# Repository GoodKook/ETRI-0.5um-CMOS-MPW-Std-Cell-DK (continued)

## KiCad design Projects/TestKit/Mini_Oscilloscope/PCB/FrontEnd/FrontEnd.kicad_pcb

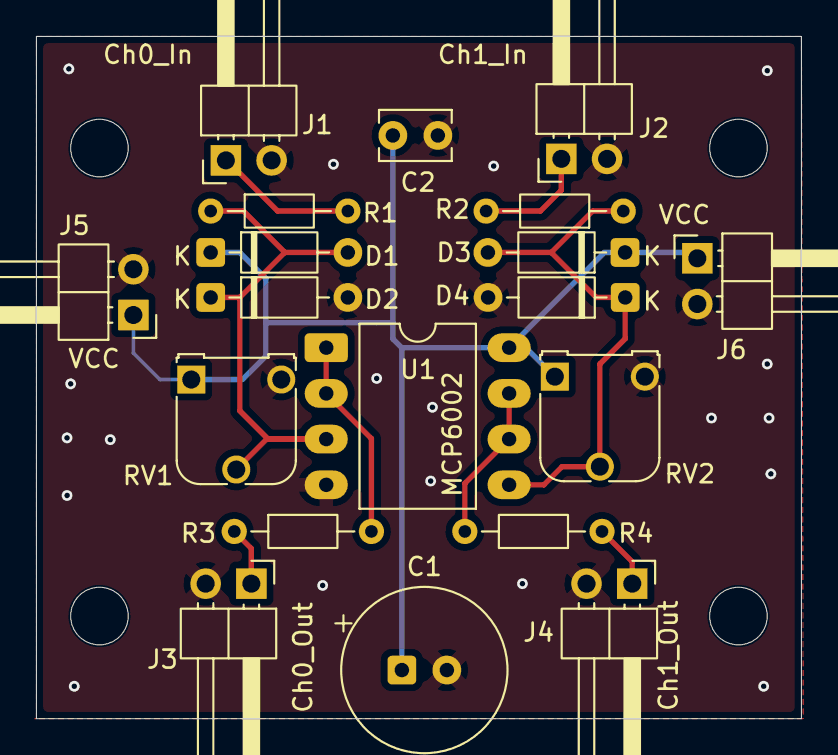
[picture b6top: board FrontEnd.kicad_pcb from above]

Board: 2 copper layers, 42.5 x 37.9 mm, 23 parts (0 on the bottom side), 10 nets.

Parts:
C1: 10u; CP_Radial_Tantal_D9.0mm_P2.50mm
C2: 100n; C_Disc_D3.8mm_W2.6mm_P2.50mm
D1, D2, D3, D4: 1N4148; D_DO-35_SOD27_P7.62mm_Horizontal
J1: Ch0_In; PinHeader_1x02_P2.54mm_Horizontal
J2: Ch1_In; PinHeader_1x02_P2.54mm_Horizontal
J3: Ch0_Out; PinHeader_1x02_P2.54mm_Horizontal
J4: Ch1_Out; PinHeader_1x02_P2.54mm_Horizontal
J5, J6: VCC; PinHeader_1x02_P2.54mm_Horizontal
R1, R2: 680K; R_Axial_DIN0204_L3.6mm_D1.6mm_P7.62mm_Horizontal
R3, R4: 100; R_Axial_DIN0204_L3.6mm_D1.6mm_P7.62mm_Horizontal
RV1, RV2: 1M; Potentiometer_Runtron_RM-065_Vertical
TP1, TP2, TP3, TP4: Mounting Hole; MountingHole_3.2mm_M3
U1: MCP6002; DIP-8_W10.16mm_LongPads

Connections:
/ADC_0: J3.1, R3.1
/ADC_1: J4.1, R4.1
GND: C1.2, C2.2, D2.2 (A), D4.2 (A), J1.2, J2.2, J3.2, J4.2, J5.2, J6.2, RV1.3, RV2.3, U1.4 (V-)
unnamed: D1.2 (A), D2.1 (K), R1.1, RV1.2, U1.3 (+)
unnamed: D3.2 (A), D4.1 (K), R2.1, RV2.2, U1.5 (+)
unnamed: J1.1, R1.2
unnamed: J2.1, R2.2
unnamed: R3.2, U1.1, U1.2 (-)
unnamed: R4.2, U1.6 (-), U1.7
VCC: C1.1, C2.1, D1.1 (K), D3.1 (K), J5.1, J6.1, RV1.1, RV2.1, U1.8 (V+)

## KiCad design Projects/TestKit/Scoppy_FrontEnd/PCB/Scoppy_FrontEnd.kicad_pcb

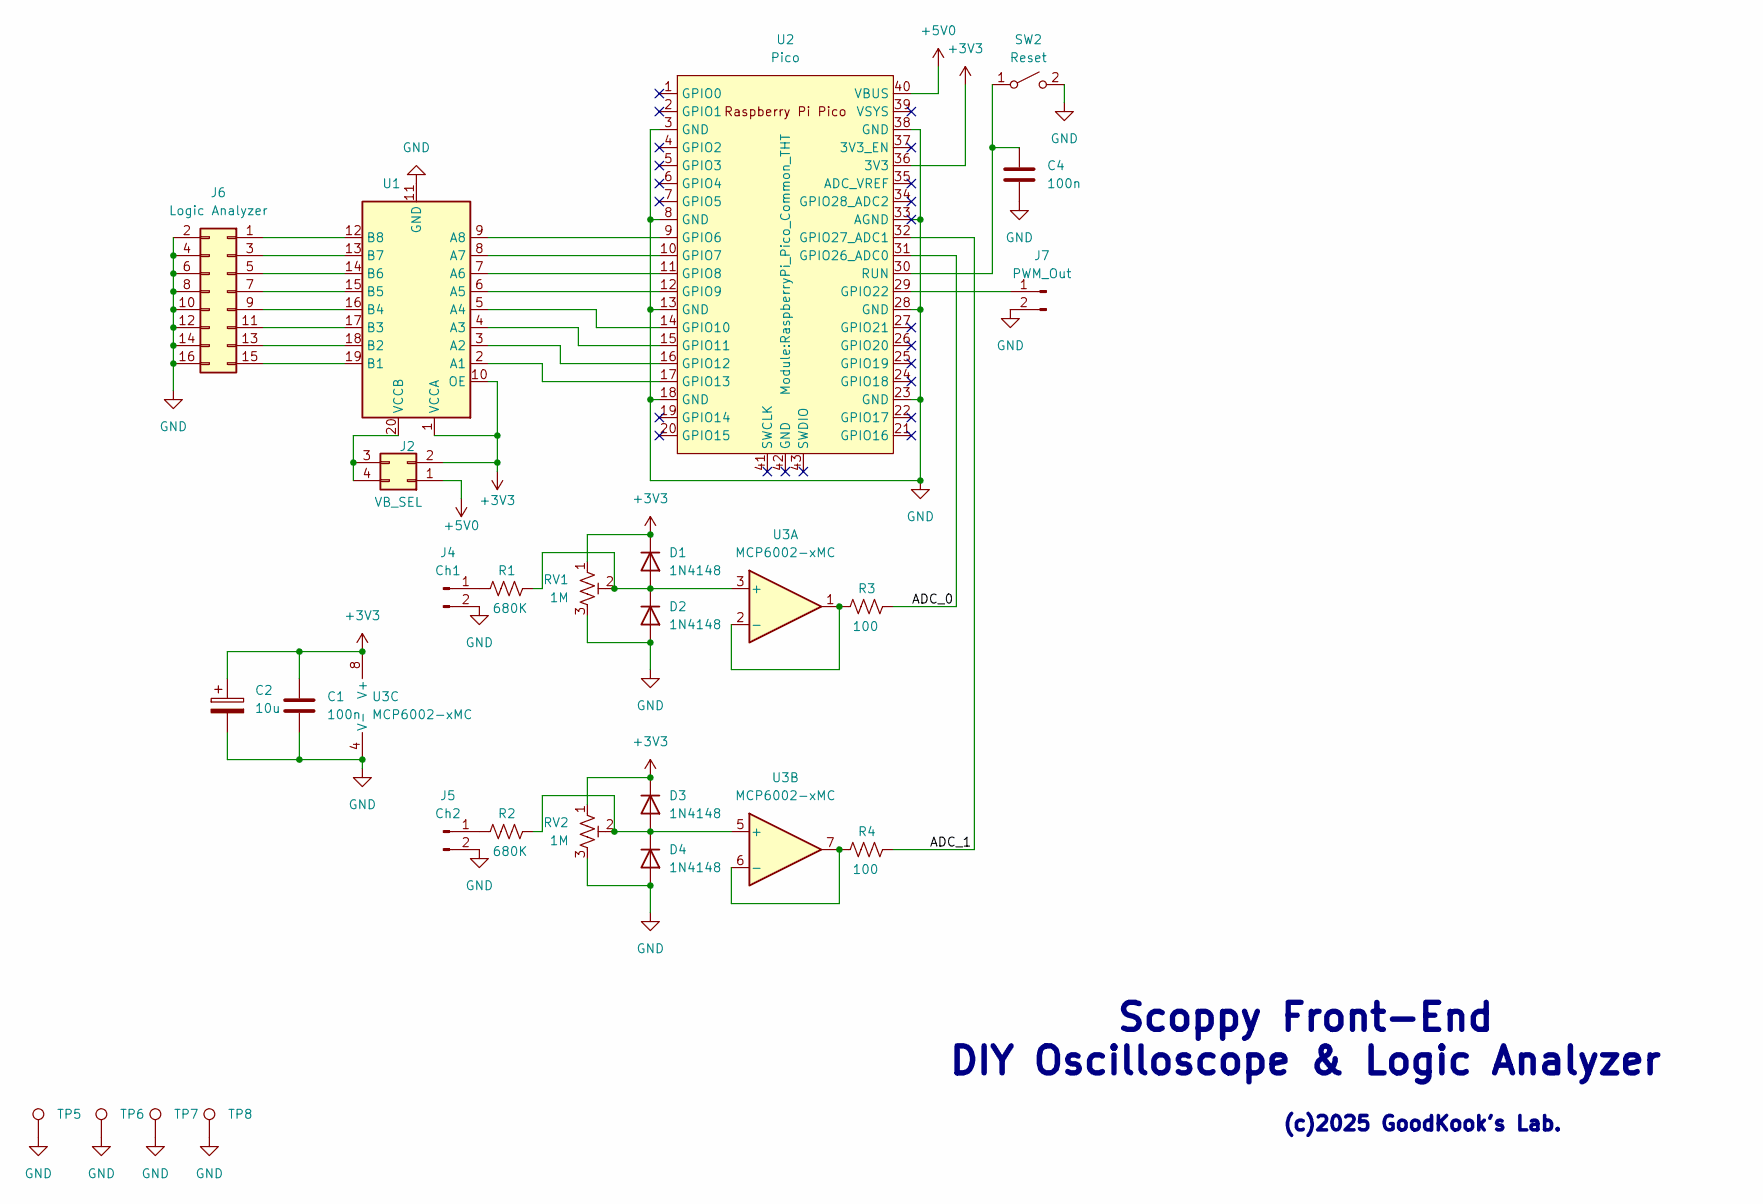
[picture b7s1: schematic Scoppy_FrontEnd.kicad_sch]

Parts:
C1, C4: 100n; C_Disc_D3.8mm_W2.6mm_P2.50mm
C2: 10u; CP_Radial_Tantal_D9.0mm_P2.50mm
D1, D2, D3, D4: 1N4148; D_DO-35_SOD27_P7.62mm_Horizontal
J2: VB_SEL; PinHeader_2x02_P2.54mm_Vertical
J4: Ch1; PinHeader_2x01_P2.54mm_Vertical
J5: Ch2; PinHeader_2x01_P2.54mm_Vertical
J6: Logic Analyzer; PinHeader_2x08_P2.54mm_Vertical
J7: PWM_Out; PinHeader_2x01_P2.54mm_Vertical
R1, R2: 680K; R_Axial_DIN0204_L3.6mm_D1.6mm_P7.62mm_Horizontal
R3, R4: 100; R_Axial_DIN0204_L3.6mm_D1.6mm_P7.62mm_Horizontal
RV1, RV2: 1M; Potentiometer_Runtron_RM-065_Vertical
SW2: Reset; SW_PUSH_6mm_H5mm
TP5, TP6, TP7, TP8: Mounting Hole; MountingHole_3.2mm_M3
U1: Level_Shifter_Module_HW-221
U2: Pico; RaspberryPi_Pico_Common_THT
U3: MCP6002-xMC; DIP-8_W10.16mm_LongPads

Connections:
+3V3: C1.1, C2.1, D1.1 (K), D3.1 (K), J2.2, RV1.1, RV2.1, U1.1 (VCCA), U1.10 (OE), U2.36 (3V3), U3.8 (V+)
+5V0: J2.1, U2.40 (VBUS)
/ADC_0: R3.1, U2.31 (GPIO26_ADC0)
/ADC_1: R4.1, U2.32 (GPIO27_ADC1)
GND: C1.2, C2.2, C4.2, D2.2 (A), D4.2 (A), J4.2, J5.2, J6.2, J6.4, J6.6, J6.8, J6.10, J6.12, J6.14, J6.16, J7.2, RV1.3, RV2.3, SW2.2 (B), TP5.1, TP6.1, TP7.1, TP8.1, U1.11 (GND), U2.3 (GND), U2.8 (GND), U2.13 (GND), U2.18 (GND), U2.23 (GND), U2.28 (GND), U2.33 (AGND), U2.38 (GND), U3.4 (V-), U3.9 (V-)
unnamed: D1.2 (A), D2.1 (K), R1.1, RV1.2, U3.3 (+)
unnamed: D3.2 (A), D4.1 (K), R2.1, RV2.2, U3.5 (+)
unnamed: J2.3, J2.4, U1.20 (VCCB)
unnamed: J4.1, R1.2
unnamed: J5.1, R2.2
unnamed: J6.1, U1.12 (B8)
unnamed: J6.3, U1.13 (B7)
unnamed: J6.5, U1.14 (B6)
unnamed: J6.7, U1.15 (B5)
unnamed: J6.9, U1.16 (B4)
unnamed: J6.11, U1.17 (B3)
unnamed: J6.13, U1.18 (B2)
unnamed: J6.15, U1.19 (B1)
unnamed: J7.1, U2.29 (GPIO22)
unnamed: C4.1, SW2.1 (A), U2.30 (RUN)
unnamed: U1.2 (A1), U2.17 (GPIO13)
unnamed: U1.3 (A2), U2.16 (GPIO12)
unnamed: U1.4 (A3), U2.15 (GPIO11)
unnamed: U1.5 (A4), U2.14 (GPIO10)
unnamed: U1.6 (A5), U2.12 (GPIO9)
unnamed: U1.7 (A6), U2.11 (GPIO8)
unnamed: U1.8 (A7), U2.10 (GPIO7)
unnamed: U1.9 (A8), U2.9 (GPIO6)
unnamed: R3.2, U3.1, U3.2 (-)
unnamed: R4.2, U3.6 (-), U3.7

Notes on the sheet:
Scoppy Front-End DIY Oscilloscope & Logic Analyzer
(c)2025 GoodKook's Lab.

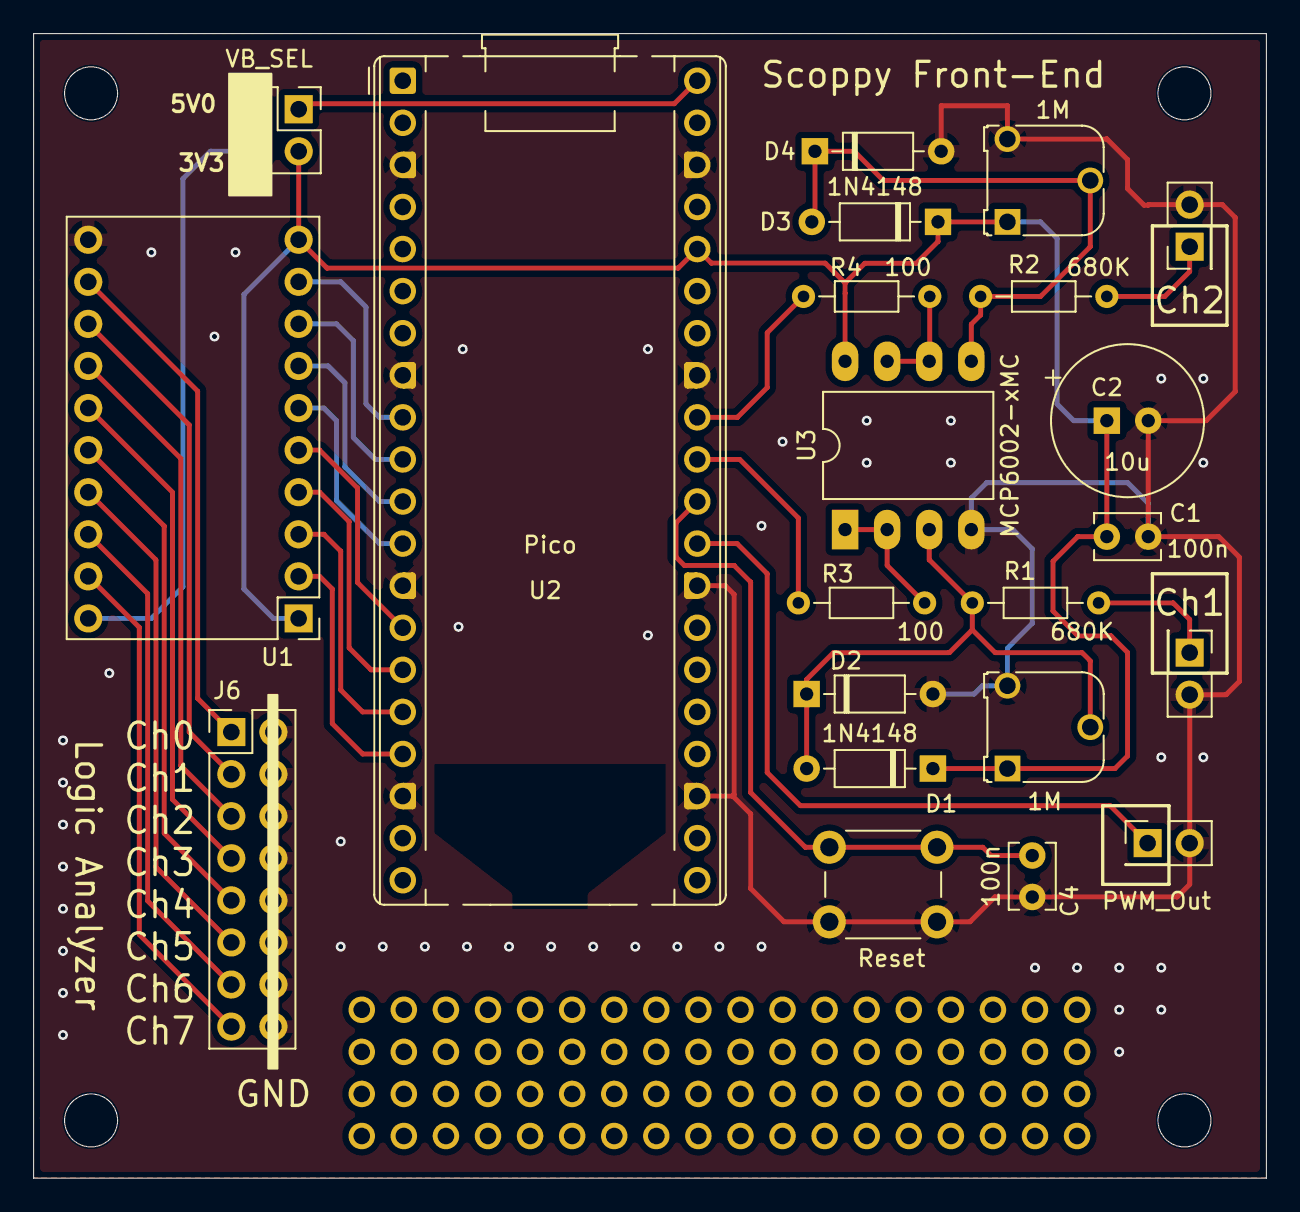
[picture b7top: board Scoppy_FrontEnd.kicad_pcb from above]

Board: 2 copper layers, 74.4 x 69.1 mm, 26 parts (0 on the bottom side), 30 nets.

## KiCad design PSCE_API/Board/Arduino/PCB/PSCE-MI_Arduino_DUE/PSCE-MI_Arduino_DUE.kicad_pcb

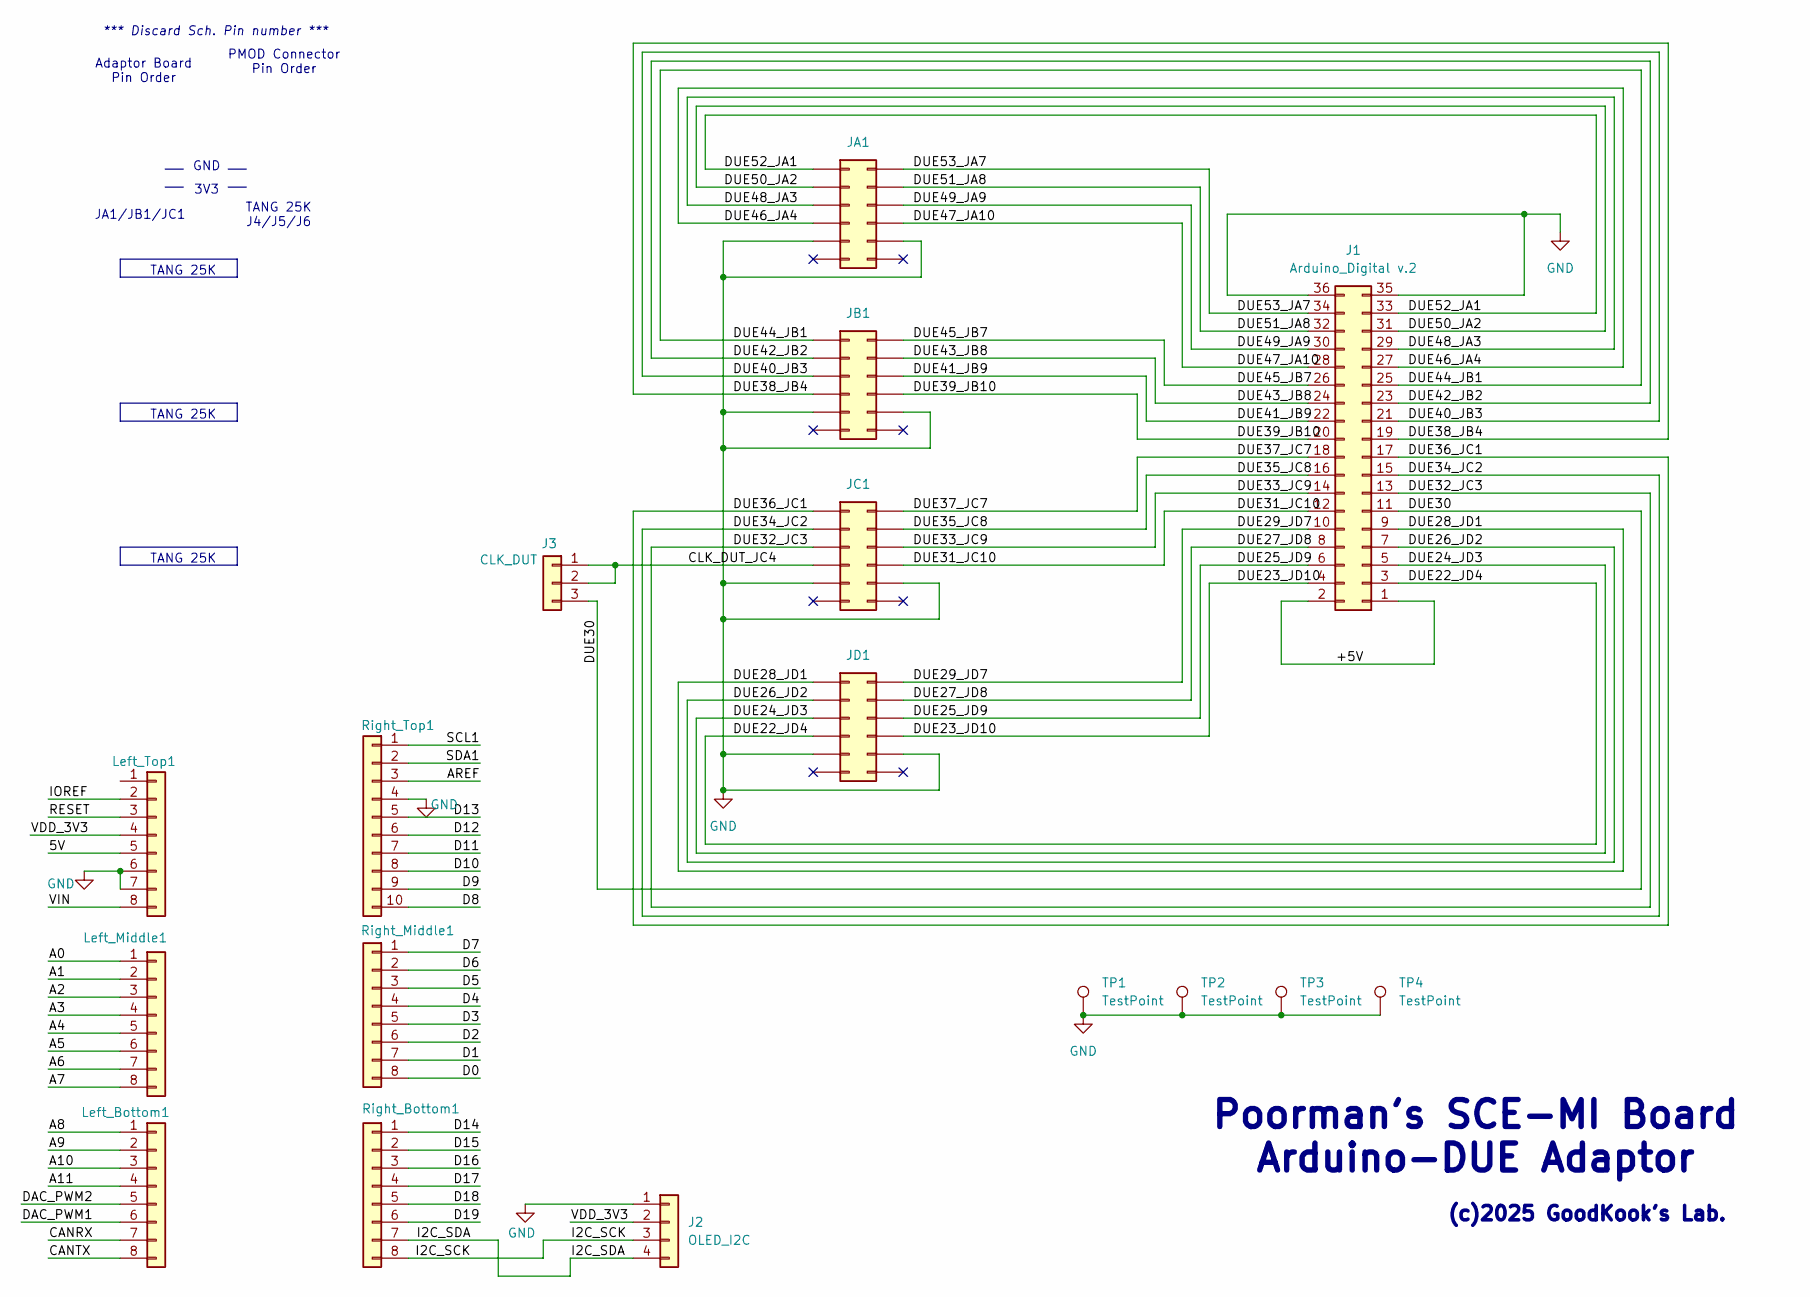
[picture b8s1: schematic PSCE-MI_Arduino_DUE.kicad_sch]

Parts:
J1: Arduino_Digital v.2; PinHeader_2x18_P2.54mm_Vertical
J2: OLED_I2C; PinHeader_1x04_P2.54mm_Vertical
J3: CLK_DUT; PinHeader_1x03_P2.54mm_Vertical
JA1: A7_JA; PinHeader_2x06_P2.54mm_Vertical
JB1: A7_JB; PinHeader_2x06_P2.54mm_Vertical
JC1: A7_JC; PinHeader_2x06_P2.54mm_Vertical
JD1: A7_JD; PinHeader_2x06_P2.54mm_Vertical
Left_Bottom1: Conn_01x08; PinHeader_1x08_P2.54mm_Vertical
Left_Middle1: Conn_01x08; PinHeader_1x08_P2.54mm_Vertical
Left_Top1: Conn_01x08; PinHeader_1x08_P2.54mm_Vertical
Right_Bottom1: Conn_01x08; PinHeader_1x08_P2.54mm_Vertical
Right_Middle1: Conn_01x08; PinHeader_1x08_P2.54mm_Vertical
Right_Top1: Conn_01x10; PinHeader_1x10_P2.54mm_Vertical
TP1, TP2, TP4: TestPoint; TestPoint_Plated_Hole_D3.0mm
TP3: TestPoint; TestPoint_Bridge_Pitch7.62mm_Drill1.3mm

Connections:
/5V: Left_Top1.5
/+5V: J1.1, J1.2
/A0: Left_Middle1.1
/A1: Left_Middle1.2
/A2: Left_Middle1.3
/A3: Left_Middle1.4
/A4: Left_Middle1.5
/A5: Left_Middle1.6
/A6: Left_Middle1.7
/A7: Left_Middle1.8
/A8: Left_Bottom1.1
/A9: Left_Bottom1.2
/A10: Left_Bottom1.3
/A11: Left_Bottom1.4
/AREF: Right_Top1.3
/CANRX: Left_Bottom1.7
/CANTX: Left_Bottom1.8
/CLK_DUT_JC4: J3.1, J3.2, JC1.7
/D0: Right_Middle1.8
/D1: Right_Middle1.7
/D2: Right_Middle1.6
/D3: Right_Middle1.5
/D4: Right_Middle1.4
/D5: Right_Middle1.3
/D6: Right_Middle1.2
/D7: Right_Middle1.1
/D8: Right_Top1.10
/D9: Right_Top1.9
/D10: Right_Top1.8
/D11: Right_Top1.7
/D12: Right_Top1.6
/D13: Right_Top1.5
/D14: Right_Bottom1.1
/D15: Right_Bottom1.2
/D16: Right_Bottom1.3
/D17: Right_Bottom1.4
/D18: Right_Bottom1.5
/D19: Right_Bottom1.6
/DAC_PWM1: Left_Bottom1.6
/DAC_PWM2: Left_Bottom1.5
/DUE22_JD4: J1.3, JD1.7
/DUE23_JD10: J1.4, JD1.8
/DUE24_JD3: J1.5, JD1.5
/DUE25_JD9: J1.6, JD1.6
/DUE26_JD2: J1.7, JD1.3
/DUE27_JD8: J1.8, JD1.4
/DUE28_JD1: J1.9, JD1.1
/DUE29_JD7: J1.10, JD1.2
/DUE30: J1.11, J3.3
/DUE31_JC10: J1.12, JC1.8
/DUE32_JC3: J1.13, JC1.5
/DUE33_JC9: J1.14, JC1.6
/DUE34_JC2: J1.15, JC1.3
/DUE35_JC8: J1.16, JC1.4
/DUE36_JC1: J1.17, JC1.1
/DUE37_JC7: J1.18, JC1.2
/DUE38_JB4: J1.19, JB1.7
/DUE39_JB10: J1.20, JB1.8
/DUE40_JB3: J1.21, JB1.5
/DUE41_JB9: J1.22, JB1.6
/DUE42_JB2: J1.23, JB1.3
/DUE43_JB8: J1.24, JB1.4
/DUE44_JB1: J1.25, JB1.1
/DUE45_JB7: J1.26, JB1.2
/DUE46_JA4: J1.27, JA1.7
/DUE47_JA10: J1.28, JA1.8
/DUE48_JA3: J1.29, JA1.5
/DUE49_JA9: J1.30, JA1.6
/DUE50_JA2: J1.31, JA1.3
/DUE51_JA8: J1.32, JA1.4
/DUE52_JA1: J1.33, JA1.1
/DUE53_JA7: J1.34, JA1.2
/I2C_SCK: J2.3, Right_Bottom1.8
/I2C_SDA: J2.4, Right_Bottom1.7
/IOREF: Left_Top1.2
/RESET: Left_Top1.3
/SCL1: Right_Top1.1
/SDA1: Right_Top1.2
/VDD_3V3: J2.2, Left_Top1.4
/VIN: Left_Top1.8
GND: J1.35, J1.36, J2.1, JA1.9, JA1.10, JB1.9, JB1.10, JC1.9, JC1.10, JD1.9, JD1.10, Left_Top1.6, Left_Top1.7, Right_Top1.4, TP1.1, TP2.1, TP3.1, TP4.1

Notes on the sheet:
TANG 25K J4/J5/J6
PMOD Connector Pin Order
*** Discard Sch. Pin number ***
TANG 25K
JA1/JB1/JC1
Adaptor Board Pin Order
GND
(c)2025 GoodKook's Lab.
3V3
Poorman's SCE-MI Board Arduino-DUE Adaptor

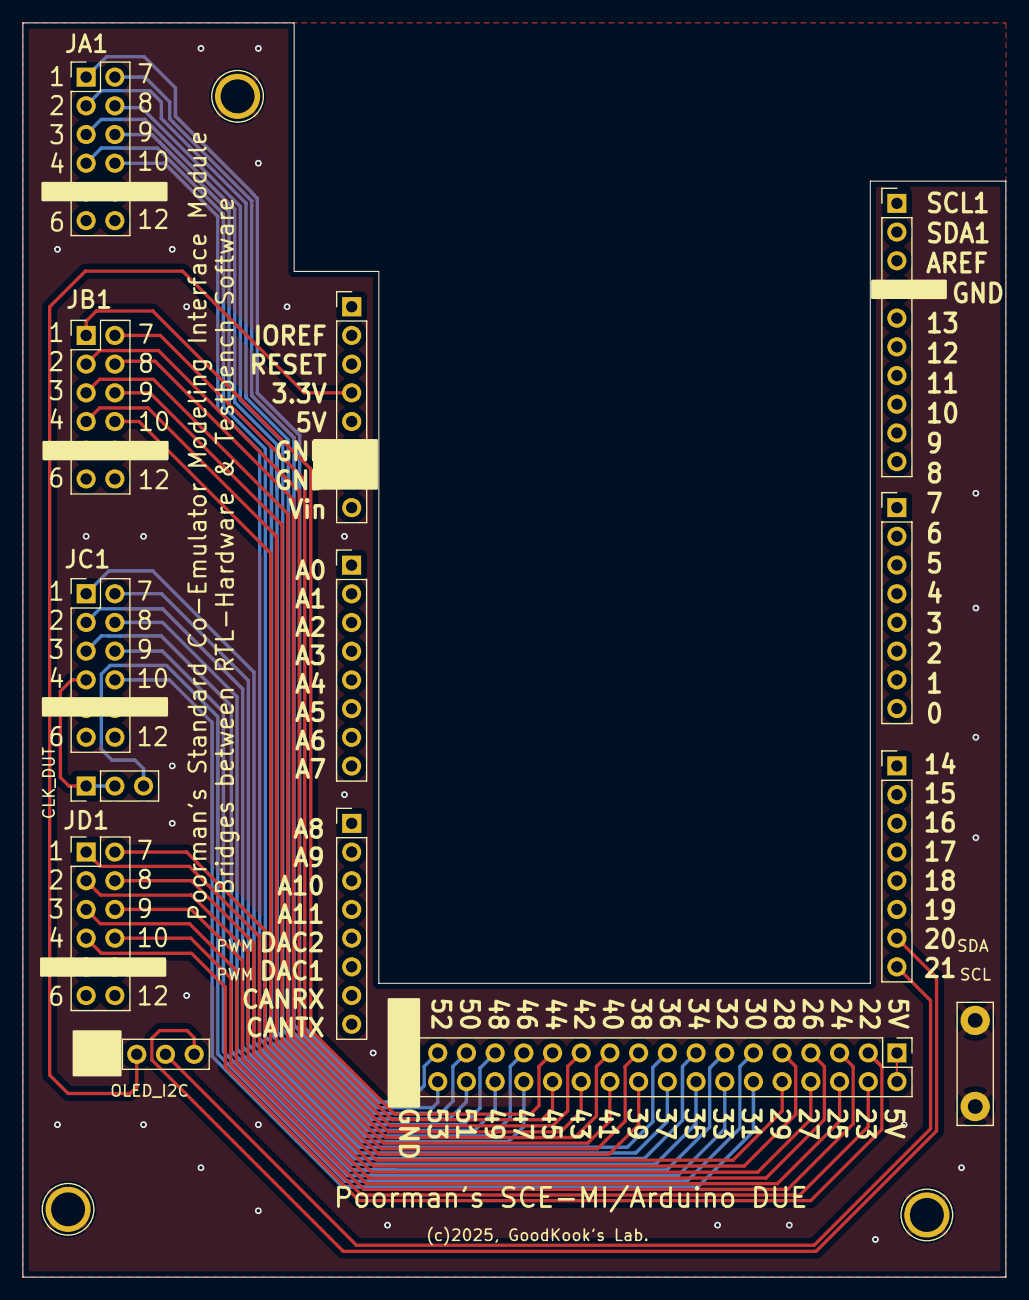
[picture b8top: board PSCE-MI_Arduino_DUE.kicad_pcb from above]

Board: 2 copper layers, 87.0 x 111.0 mm, 17 parts (0 on the bottom side), 38 nets.

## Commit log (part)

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2024-09-28 Version.E
2024-10-02 Update.F
2024-10-02 Changes to be committed: modified: Tools/KiCad_Install.sh modified: Tools/arm_toolchain_install.sh modified: Tools/build_tools.sh modified: Tools/graywolf_build.sh modified: Tools/gsl_build.sh modifi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
2024-10-02 Changes to be committed: modified: digital_ETRI/extract_lef_macro.py modified: digital_ETRI/gen_lef_stdcells.py modified: digital_ETRI/link_lib.sh modified: digital_ETRI/lvl_cell.sh
2024-10-02 Changes to be committed: modified: scripts/bmp2mag.py modified: scripts/bmp2mag_m123.py modified: scripts/check_via_stack.py modified: scripts/drc_core.sh modified: scripts/ext2sim.sh modified: scrip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
2024-10-03 Updated.F
2024-10-05 Update.Fa
2024-10-05 Tech.Fa
2024-10-05 Update.Fb
2024-10-06 update.tech
2025-03-09 Update Xresources
2025-08-16 Update Makefile
2025-10-25 PCB Update
2026-01-15 Update cpu_6502
2026-01-15 Updated apple_1_WozMon
2026-05-09 Add files via upload
    Updated
2026-05-09 MNIST v2 Updated
2026-05-11 MYONN Updated
